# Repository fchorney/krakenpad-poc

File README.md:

# KrakenPad

Open-source dance pad controller hardware and firmware, built for modern ITG-style
rhythm games (Stepmania, ITGmania, DeadSync, etc.).

Commercial dance pad electronics haven't kept pace with what competitive/high-level
play actually wants: low, consistent input latency, high-resolution force sensing,
and hardware/firmware you can actually inspect, modify, and fix yourself. This
project is a ground-up replacement controller — sensor boards, main controller, and
firmware — designed around those priorities instead of around vendor lock-in or
proprietary protocols.

It is not tied to any one game or platform — it just speaks USB HID, so anything
that reads a standard controller/joystick works.

## Priorities

- **Low, consistent input latency.** Presses are detected and reported by dedicated
  interrupt-driven hardware, not discovered via a slow polling cycle — eliminating
  the multi-millisecond blind spots that periodic-scan designs are prone to.
- **High-resolution force sensing.** Each panel reads continuous per-sensor
  pressure (not just a binary switch), sampled at kHz-class rates, enabling more
  accurate and tunable press/release detection than simple threshold switches.
- **Higher, more consistent USB polling and LED refresh rates** than older
  commercial hardware typically offers, for tighter timing and smoother panel
  lighting.
- **Fully open hardware and firmware.** Schematics, PCB layouts, and firmware
  source are all open — no proprietary authentication, no closed protocol, no
  black-box firmware blobs. Anyone can build, modify, or repair their own unit.
- **Standard, open software compatibility.** Presents as a generic USB controller
  so it works out of the box with the open-source rhythm game ecosystem, with no
  vendor-specific driver or SDK required.

## Hardware Scope

The project is initially targeted at retrofitting existing SMX-style dance pad
frames — reusing the frame and panel mechanics while replacing the electronics
(control unit and panel sensor/LED boards) entirely. The design isn't
SMX-compatible at the protocol or hardware level; it simply fits the same
frame as a drop-in electronics replacement, since that's the hardware most
readily available for this kind of upgrade.

## Status

Rev 1 of both boards (the master controller and the two-board panel) was
fabricated in August 2026 and is the hardware in use. A full set of nine panels
and a master run together on the bench: presses reach the PC as a USB joystick,
all nine panels share one RS-485 bus with no errors, and new panel firmware is
flashed to the whole pad over that bus. Written but not yet run on the
hardware: live sensor telemetry and configuration over USB, with the settings
saved on the master. Not written yet: local panel animations. Any board change
from here is a rev 2 change.

Current state and next steps: `docs/STATUS.md`. Per-board results:
`docs/BRINGUP_LOG.md`. Design notes and specs: `CLAUDE.md` and `docs/`.

## AI Disclosure

This project was built with AI assistance (Claude), used mainly for the grunt
work: research and part-comparison legwork, documentation drafts, firmware
prototyping, design-review passes, and scripted KiCad edits/fab outputs. All
design decisions, schematic wiring, PCB layout, and physical testing were done
by a human.

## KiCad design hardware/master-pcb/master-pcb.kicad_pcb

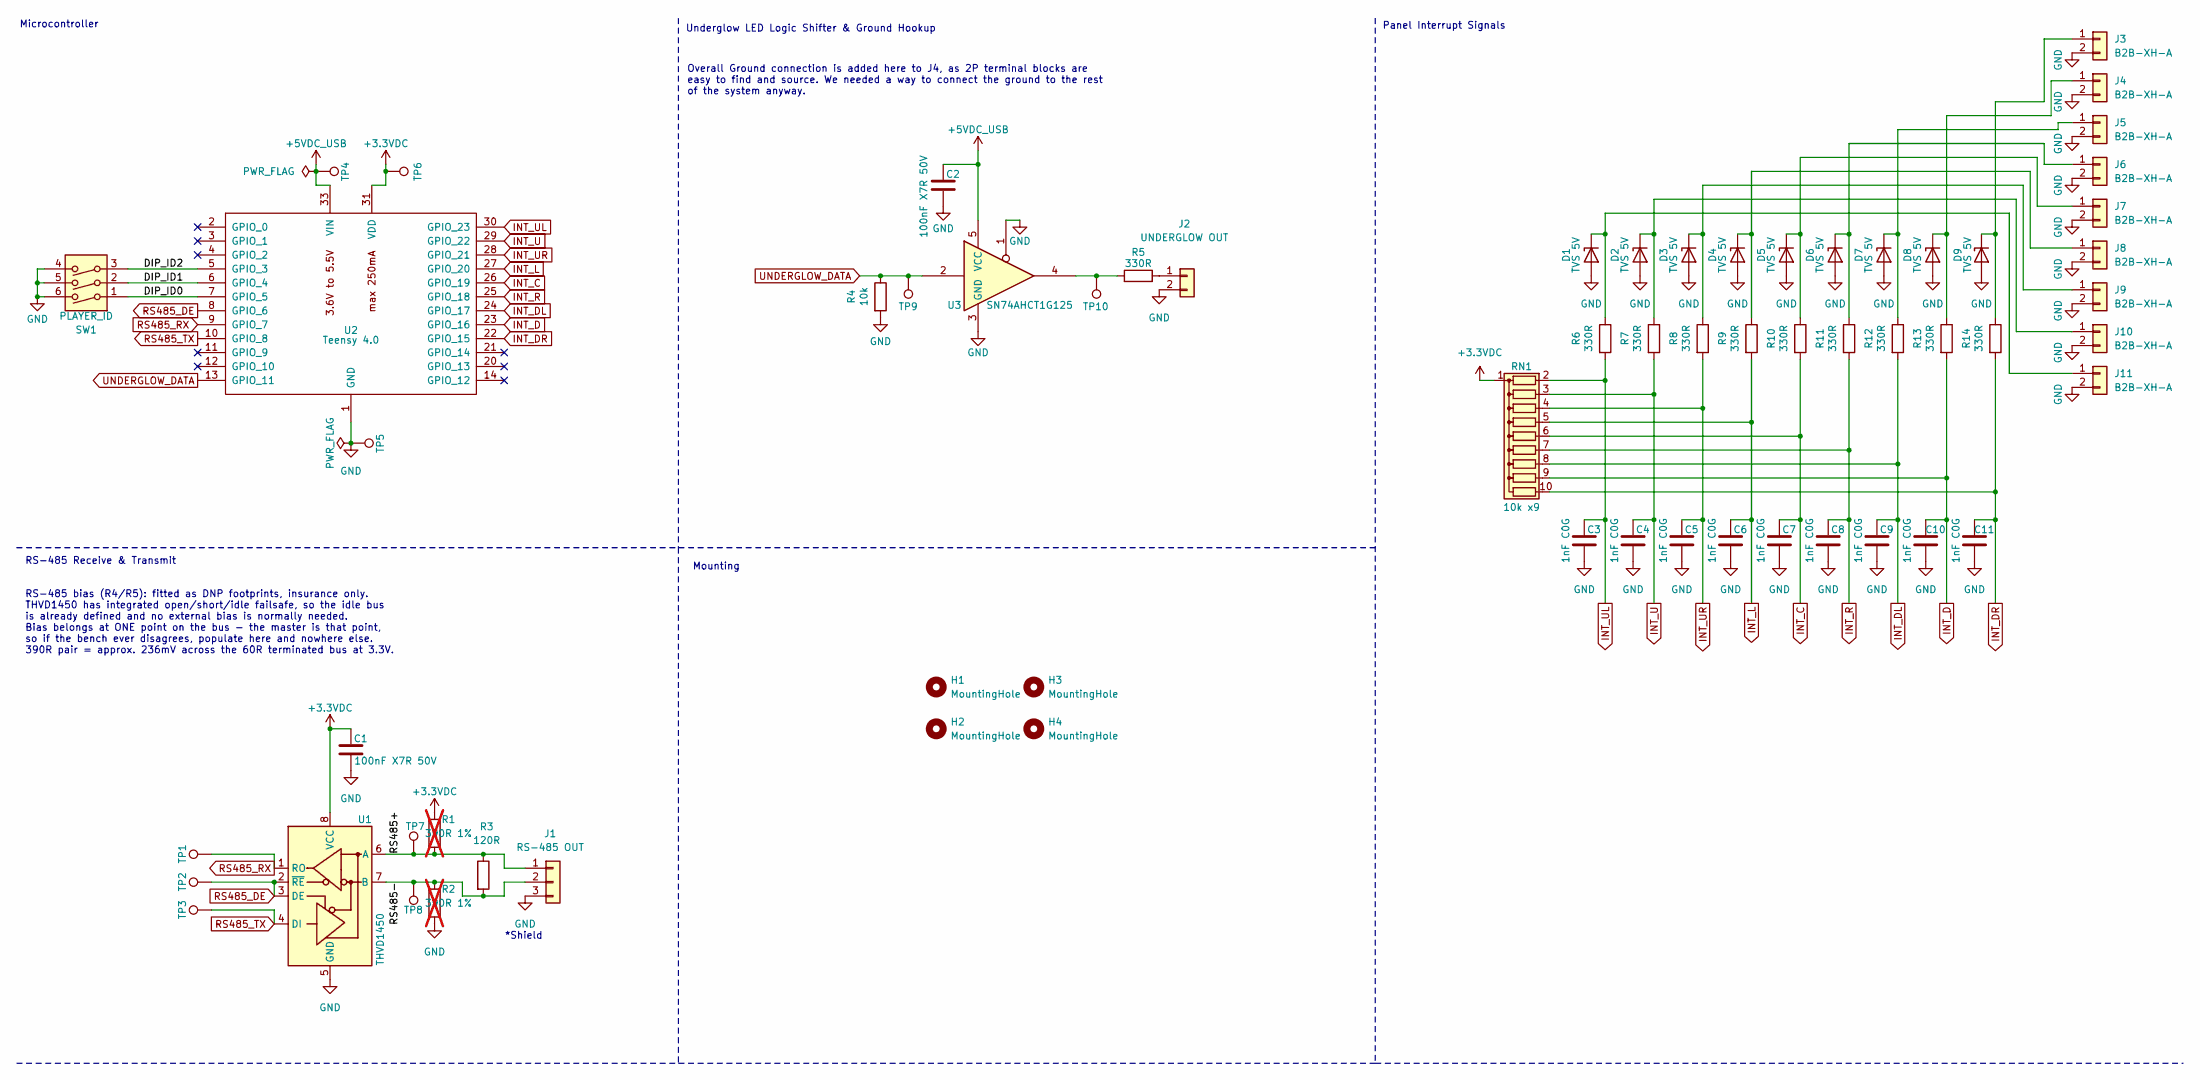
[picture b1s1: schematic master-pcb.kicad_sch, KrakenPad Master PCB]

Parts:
C1, C2: 100nF X7R 50V; C_0805_2012Metric; LCSC C83055
C3, C4, C5, C6, C7, C8, C9, C10, C11: 1nF C0G; C_0805_2012Metric; LCSC C1791
D1, D2, D3, D4, D5, D6, D7, D8, D9: TVS 5V; D_SMA_Handsoldering; MPN SMAJ5.0A; LCSC C113952
H1, H2, H3, H4: MountingHole; MountingHole_3.2mm_M3
J1: RS-485 OUT; Molex_Micro-Fit_3.0_43650-0300_1x03_P3.00mm_Horizontal; MPN 0436500300; LCSC C503478
J2: UNDERGLOW OUT; TerminalBlock_WJ500V-5.08-2P; MPN WJ500V-5.08-2P; LCSC C8465
J3, J4, J5, J6, J7, J8, J9, J10, J11: B2B-XH-A; JST_XH_B2B-XH-A_1x02_P2.50mm_Vertical; LCSC C158012
R1, R2: 390R 1%; R_0805_2012Metric; not fitted
R3: 120R; R_0805_2012Metric; LCSC C844816
R4: 10k; R_0805_2012Metric; LCSC C192906
R5, R6, R7, R8, R9, R10, R11, R12, R13, R14: 330R; R_0805_2012Metric; LCSC C844839
RN1: 10k x9; R_Array_SIP10; MPN 4610X-101-103LF; LCSC C840655
SW1: PLAYER_ID; SW_DIP_SPSTx03_Slide_9.78x9.8mm_W7.62mm_P2.54mm; MPN DS-3P-BU; LCSC C46595747
TP1: RS-485 RX; TestPoint_THTPad_D2.0mm_Drill1.0mm
TP2: RS-485 DE; TestPoint_THTPad_D2.0mm_Drill1.0mm
TP3: RS-485 TX; TestPoint_THTPad_D2.0mm_Drill1.0mm
TP4: +5VDC_USB; TestPoint_THTPad_D2.0mm_Drill1.0mm
TP5: GND; TestPoint_THTPad_D2.0mm_Drill1.0mm
TP6: +3.3VDC; TestPoint_THTPad_D2.0mm_Drill1.0mm
TP7: RS-485 A; TestPoint_THTPad_D2.0mm_Drill1.0mm
TP8: RS-485 B; TestPoint_THTPad_D2.0mm_Drill1.0mm
TP9: Underglow DATA 3.3V; TestPoint_THTPad_D2.0mm_Drill1.0mm
TP10: Underglow DATA 5V; TestPoint_THTPad_D2.0mm_Drill1.0mm
U1: THVD1450; SOIC-8_3.9x4.9mm_P1.27mm; MPN THVD1450DR; LCSC C2671361
U2: Teensy 4.0; Teensy40_Socketed; MPN 15583; DigiKey 1568-15583-ND
U3: SN74AHCT1G125; SOT-23-5; MPN SN74AHCT1G125DBVR; LCSC C7484

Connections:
+3.3VDC: C1.1, R1.1, RN1.1 (common), TP6.1 (1_1), U1.8 (VCC), U2.31 (VDD)
+5VDC_USB: C2.1, TP4.1 (1_1), U2.33 (VIN), U3.5 (VCC)
/DIP_ID0: SW1.1, U2.7 (GPIO_5)
/DIP_ID1: SW1.2, U2.6 (GPIO_4)
/DIP_ID2: SW1.3, U2.5 (GPIO_3)
/RS485+: J1.1, R1.2, R3.1, TP7.1 (1_1), U1.6 (A)
/RS485-: J1.2, R2.1, R3.2, TP8.1 (1_1), U1.7 (B)
GND: C1.2, C2.2, C3.2, C4.2, C5.2, C6.2, C7.2, C8.2, C9.2, C10.2, C11.2, D1.2 (A), D2.2 (A), D3.2 (A), D4.2 (A), D5.2 (A), D6.2 (A), D7.2 (A), D8.2 (A), D9.2 (A), J1.3, J2.2, J3.2, J4.2, J5.2, J6.2, J7.2, J8.2, J9.2, J10.2, J11.2, R2.2, R4.2, SW1.4, SW1.5, SW1.6, TP5.1 (1_1), U1.5 (GND), U2.1 (GND), U2.32 (GND), U3.1, U3.3 (GND)
INT_C: C7.1, R10.2, RN1.6 (R5), U2.26 (GPIO_19)
INT_D: C10.1, R13.2, RN1.9 (R8), U2.23 (GPIO_16)
INT_DL: C9.1, R12.2, RN1.8 (R7), U2.24 (GPIO_17)
INT_DR: C11.1, R14.2, RN1.10 (R9), U2.22 (GPIO_15)
INT_L: C6.1, R9.2, RN1.5 (R4), U2.27 (GPIO_20)
INT_R: C8.1, R11.2, RN1.7 (R6), U2.25 (GPIO_18)
INT_U: C4.1, R7.2, RN1.3 (R2), U2.29 (GPIO_22)
INT_UL: C3.1, R6.2, RN1.2 (R1), U2.30 (GPIO_23)
INT_UR: C5.1, R8.2, RN1.4 (R3), U2.28 (GPIO_21)
unnamed: D1.1 (K), J11.1, R6.1
unnamed: D2.1 (K), J10.1, R7.1
unnamed: D3.1 (K), J9.1, R8.1
unnamed: D4.1 (K), J8.1, R9.1
unnamed: D5.1 (K), J7.1, R10.1
unnamed: D6.1 (K), J6.1, R11.1
unnamed: D7.1 (K), J5.1, R12.1
unnamed: D8.1 (K), J4.1, R13.1
unnamed: D9.1 (K), J3.1, R14.1
unnamed: J2.1, R5.2
unnamed: R5.1, TP10.1 (1_1), U3.4
RS485_DE: TP2.1 (1_1), U1.2 (~RE), U1.3 (DE), U2.8 (GPIO_6)
RS485_RX: TP1.1 (1_1), U1.1 (RO), U2.9 (GPIO_7)
RS485_TX: TP3.1 (1_1), U1.4 (DI), U2.10 (GPIO_8)
UNDERGLOW_DATA: R4.1, TP9.1 (1_1), U2.13 (GPIO_11), U3.2

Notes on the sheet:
Panel Interrupt Signals
RS-485 bias (R4/R5): fitted as DNP footprints, insurance only. THVD1450 has integrated open/short/idle failsafe, so the idle bus is already defined and no external bias is normally needed. Bias belongs at ONE point on the bus - the master is that point, so if the bench ever disagrees, populate here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
Overall Ground connection is added here to J4, as 2P terminal blocks are easy to find and source. We needed a way to connect the ground to the rest of the system anyway.
Mounting
*Shield
Underglow LED Logic Shifter & Ground Hookup
Microcontroller
RS-485 Receive & Transmit

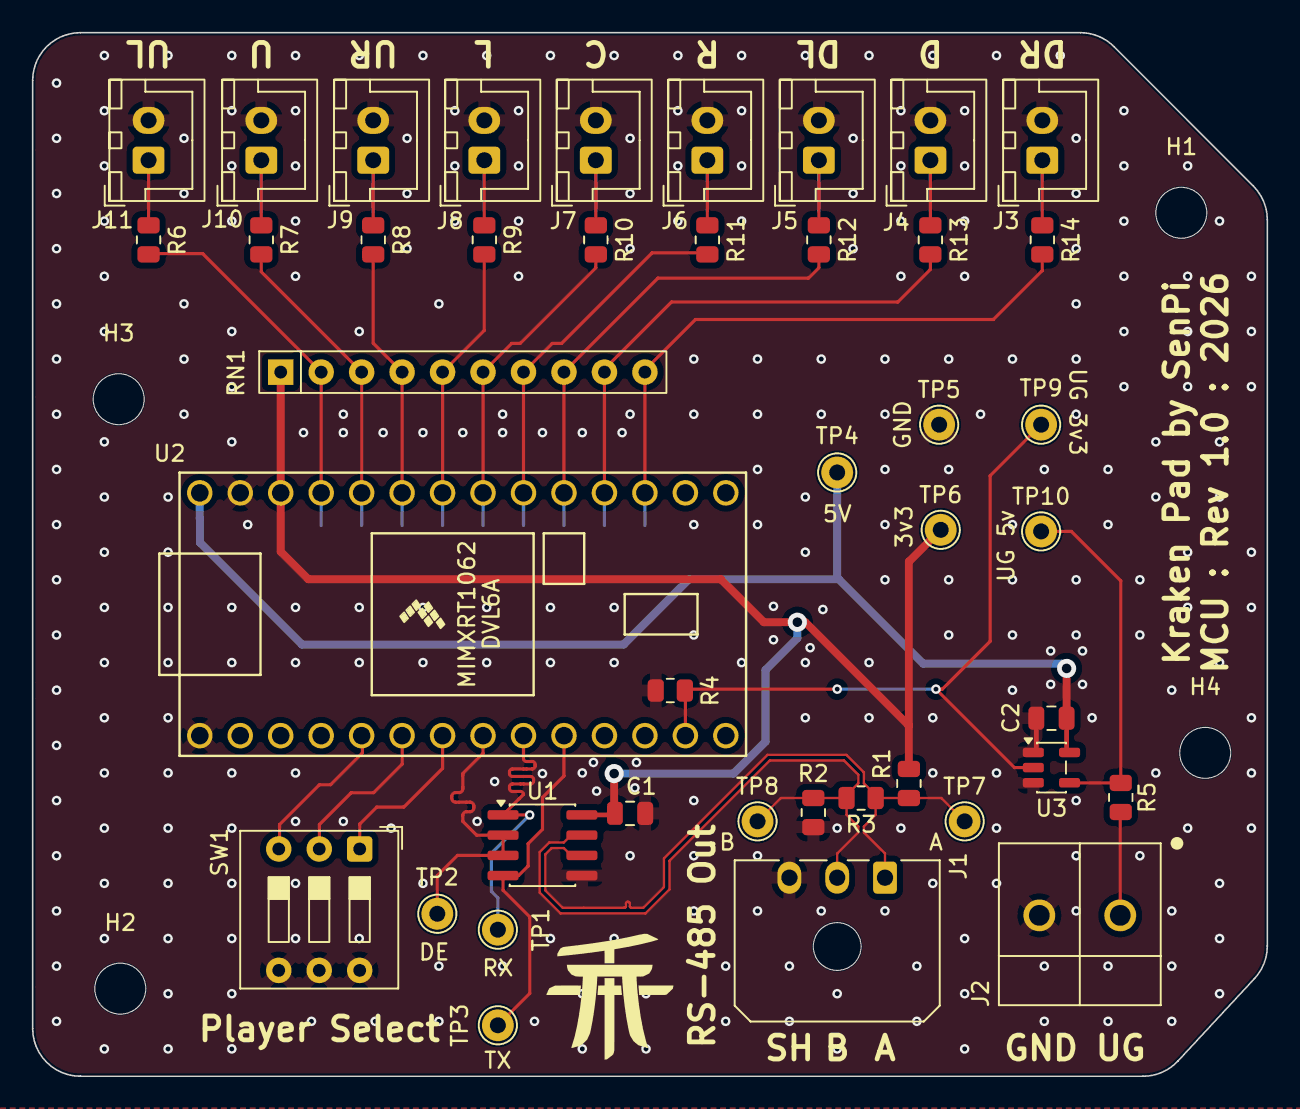
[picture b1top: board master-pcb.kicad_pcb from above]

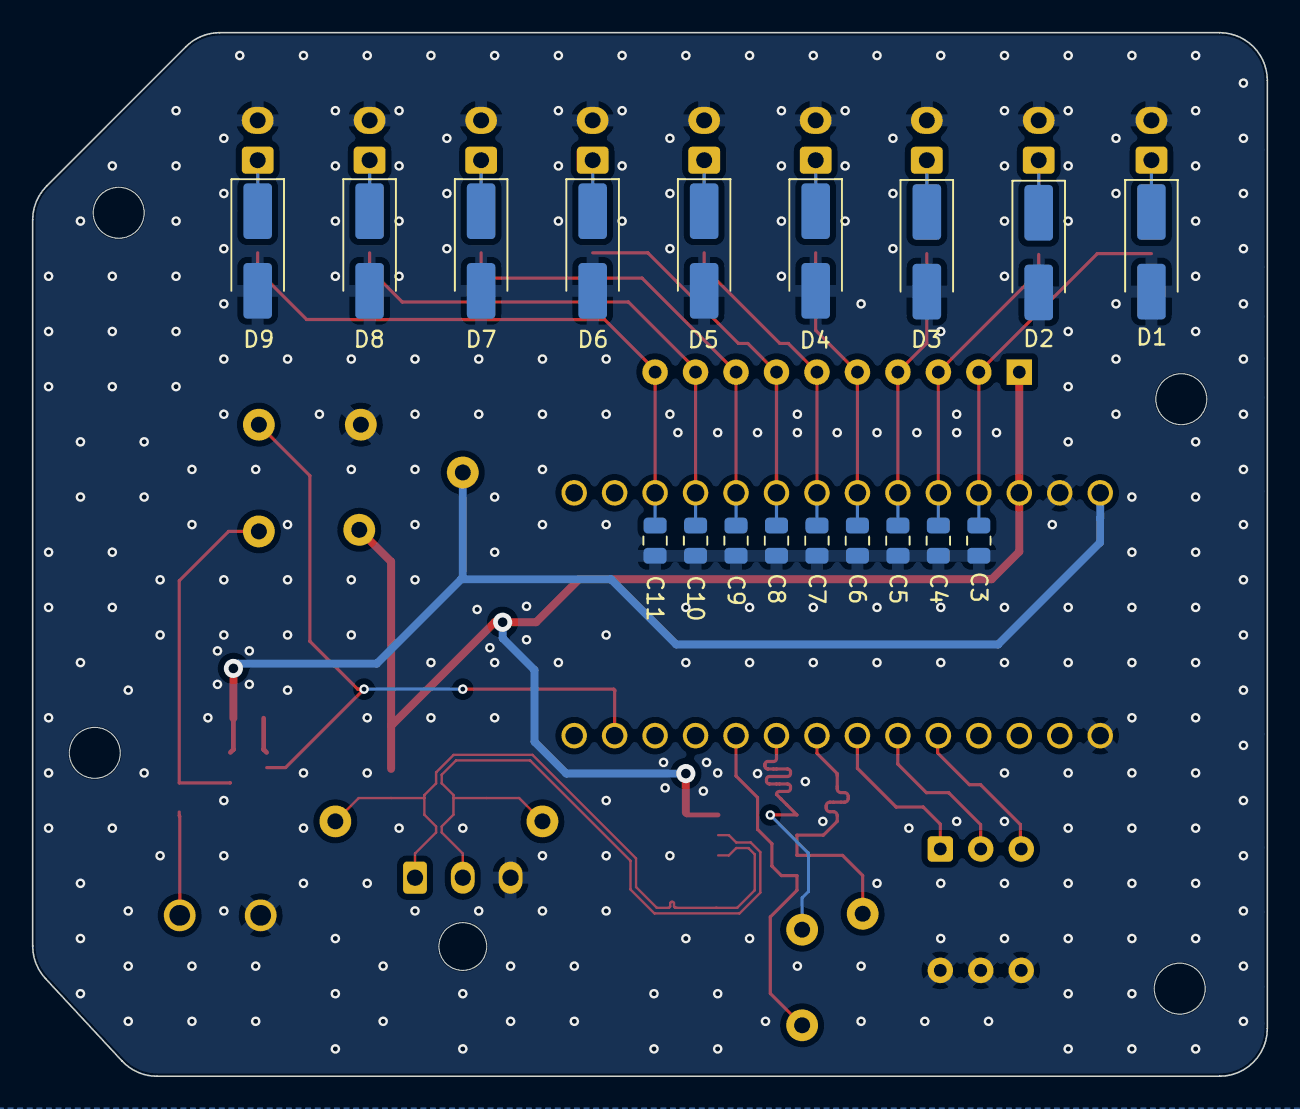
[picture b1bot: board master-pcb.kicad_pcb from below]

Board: 4 copper layers, 77.5 x 65.5 mm, 64 parts (18 on the bottom side), 32 nets.

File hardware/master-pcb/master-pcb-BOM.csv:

Qty,Refs,Value,LCSC,MPN,Source,DNP,Description
2,C1 C2,100nF X7R 50V,C83055,,LCSC,,2 per-instance descriptions
9,C3 C4 C5 C6 C7 C8 C9 C10 C11,1nF C0G,C1791,,LCSC,,9 per-instance descriptions
9,D1 D2 D3 D4 D5 D6 D7 D8 D9,TVS 5V,C113952,SMAJ5.0A,LCSC,,9 per-instance descriptions
1,J1,RS-485 OUT,C503478,0436500300,LCSC,,"Micro-Fit 3.0 THT right-angle 43650-0300; pin 3 = cable shield, tied directly to GND here; pinout must match panel J204/J207 (A=1,B=2)"
1,J2,UNDERGLOW OUT,C8465,WJ500V-5.08-2P,LCSC,,"KANGNEX WJ500V-5.08-2P (LCSC C8465), 2P 5.08mm top-entry screw terminal: GND + LED-DATA-OUT (5V logic). UI-gated; no sense pin"
9,J3 J4 J5 J6 J7 J8 J9 J10 J11,B2B-XH-A,C158012,,LCSC,,JST XH B2B-XH-A
2,R1 R2,390R 1%,,,not stocked,DNP,2 per-instance descriptions
1,R3,120R,C844816,,LCSC,,"RS-485 termination at master end, always fitted"
1,R4,10k,C192906,,LCSC,,Underglow Data Out Pulldown: To avoid sending stray high logic to Underglow LEDs before initialized.
10,R5 R6 R7 R8 R9 R10 R11 R12 R13 R14,330R,C844839,,LCSC,,10 per-instance descriptions
1,RN1,10k x9,C840655,4610X-101-103LF,LCSC,,"INT pull-ups to 3.3V, deliberately 10k not stiff (INT-into-dead-panel case); common pin to +3V3"
1,SW1,PLAYER_ID,C46595747,DS-3P-BU,LCSC,,"3-bit player/pad ID to GND, Teensy internal pull-ups; 0-3=P1-P4, 4-7 reserved"
1,U1,THVD1450,C2671361,THVD1450DR,LCSC,,"RS-485 transceiver, 3.3V; DE+/RE tied to GPIO2 net; same MPN as panel U2"
1,U2,Teensy 4.0,,15583,DigiKey,,"Teensy 4.0 development board (600MHz Cortex-M7, socketed). Symbol vendored from XenGi/teensy_library (MIT), pin numbering per PJRC pinout cards rev2; pins renamed/relaid for this project. Pins 35-54 (bottom-side SMT pads) and 15-19 (the 5-pad short-end row: VBAT, VDD, GND, PROGRAM, ON_OFF) removed to match the Teensy40_Socketed footprint and keep schematic-parity clean. 15-19 dropped 2026-07-22 to free routing area: 16/17 were stacked duplicates of the VDD/GND on pins 31/1/32, and VBAT/PROGRAM/ON_OFF are unused on this design."
1,U3,SN74AHCT1G125,C7484,SN74AHCT1G125DBVR,LCSC,,Single Bus Buffer Gate With 3-State Output

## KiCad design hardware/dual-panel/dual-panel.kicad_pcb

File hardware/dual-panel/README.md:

# Dual-board panel — the panel design

**This is the panel in use (rev 1, nine assembled).** The single-board alternative
(`hardware/panel-pcb`) was retired on 2026-08-04; it lives in git history only,
last present at `1b41d1c`.

**For as-built facts — interface pin map, RP2040 GPIO map, part inventory,
mechanical stack, verification status — read [`docs/DUAL_PANEL.md`](../../docs/DUAL_PANEL.md).**
This file covers only *why the project is shaped the way it is*; anything
enumerable is derived from the KiCad files and lives in that doc, so it cannot
drift.

> Earlier revisions of this file described a 34-pin two-row interface (J12/J13),
> USB-C on the carrier, and two mounting screws. **None of that was built.** The
> interface is four 1×8 rows (32 pins), USB-C is on the brain, and there are three
> screws. Trust `docs/DUAL_PANEL.md`.

## The idea

Split the 127×127 mm panel into a **display/IO carrier** — 25 WS2815s, every
external connector, the switches — and a **brain** — RP2040, flash, transceiver,
regulators, level shifter, USB — that plugs into the carrier's underside and sits
in the frame cavity. The LEDs own the top surface; anything mounted above them
shadows the play surface.

Motivations, in the order they mattered:

1. **Layout separation.** On one board the LED field and the brain compete for the
   same planes. Split, each board's routing is a different problem.
2. **ESD and protection.** Clamp at the ports on the carrier; the brain sits behind
   the connector.
3. **Fix the brain without re-fabbing the panels.** Not about upgrades — about a
   routing or hardware bug found at bring-up. Re-spinning a small brain board is far
   cheaper in money and materials than re-spinning 20 carriers.

The measured comparison that settled single-vs-dual is archived at
[`docs/archive/DESIGN_COMPARISON.md`](../../docs/archive/DESIGN_COMPARISON.md). Short
version: cost was near-neutral at **$2.13/panel**, and the split measured *better*
on FSR isolation — 1.1× channel-length spread vs 11×, and 3.18 mm worst same-layer
clearance to LED data / 12V vs 1.06 mm.

## Why one KiCad project rather than two

KiCad has no multi-board feature, but a project is already *one hierarchy → one
netlist → one `.kicad_pcb`*, and two `Edge.Cuts` outlines in a single board file is
the supported way to panelise. Two things fall out:

- **ERC checks the board-to-board interface for you.** With two separate projects,
  every interface change means editing two schematics and hand-checking that they
  agree — and the interface spec is precisely the mistake that would force *both*
  boards to be re-spun.
- **One JLC engineering fee and one PCBA setup instead of two.**

The cost is a known wart: the ratsnest draws airwires across the mating gap and DRC
reports 19 `unconnected_items`. There is no way to tell KiCad "these mate
mechanically." Giving each side distinct net names would kill the airwires but throw
away the cross-checking that motivated this structure, so the 19 are accepted and
enumerated instead.

## Why both boards are 4-layer on one panel

Tempting idea: carrier at 2 layers, brain at 4, since the carrier looks like it
might route single-sided. It costs more, not less, and it is not close.

A 2-layer carrier saves only the bare-fab delta on one board — the qty-5 quote put
the *entire* board cost for the 127×127 4-layer panel at **$14.91**, so even if
2-layer PCBs were free the saving caps around **$55** at qty 20; realistically
**$25–35**. A second run costs fixed per-order overhead: $25 eng fee + $51.12 PCBA
setup + $16.42 stencil + $4.93 storage ≈ **$97**, plus a second ~$40 shipment ⇒
**~$137**.

| | one 4L panel (both boards) | 2L carrier + 4L brain |
|---|---|---|
| bare fab | ~$55–60 | ~$25–30 + ~$15 |
| order overhead | $97 × 1 | $97 × 2 |
| shipping | ~$40 | ~$80 |
| **net** | — | **~$110–140 worse** |

There is no quantity where this flips: the saving scales with board count, the
penalty doesn't. Both boards need PCBA regardless — WS2815 is MSL 5a with a 24 h
floor life, so hand-assembling the carrier was never on the table.

What you get for the $25–35 you'd have "saved" is two extra copper layers on the
noisiest board in the system: an uninterrupted GND plane plus a power plane, under a
25-LED field with four high-impedance FSR lines crossing it. That is motivation #1
delivered better than the 2-layer version would have.

**6-layer was the weakest option considered** — JLCPCB lists 4-layer 100×100 mm from
~$7 vs 6-layer from ~$35, and it delivers neither the best routing environment nor
fault isolation. Only a 6-layer *brain* would genuinely force two fab runs; the brain
is already 4-layer-proven, since all of its content routed on 4 layers back when it
was still sharing them with the LED field and 12V distribution.

*Prices are point-in-time — verify live (`docs/FAB_ORDER.md` → "Money").*

## Directory map

| path | what |
|---|---|
| `dual-panel.kicad_sch` | root sheet — two sheet symbols, nothing else |
| `carrier.kicad_sch` / `brain.kicad_sch` | the two roles |
| `dual-panel.kicad_pcb` | **both** outlines, carrier left of x=182.55 mm, brain right |
| `dual-panel.pretty` / `.kicad_sym` / `3dmodels/` | project-local libraries |
| `panel/` | panelisation + JLC fab package — `gen_panel.py`, `gen_fab.py` (quotes are in `docs/rev1-order/`) |
| `fit-test/` | 1:1 printable cavity fit template — re-run after any outline change |

Both sheets were seeded as full copies of `panel-pcb` rev 1.0 and stripped to role,
which is why some schematic sheet descriptions still say so. That is history, not a
live dependency: **`dual-panel` references no `panel-pcb` library**, and its
`fp-lib-table`/`sym-lib-table` point only at its own project-local libs.

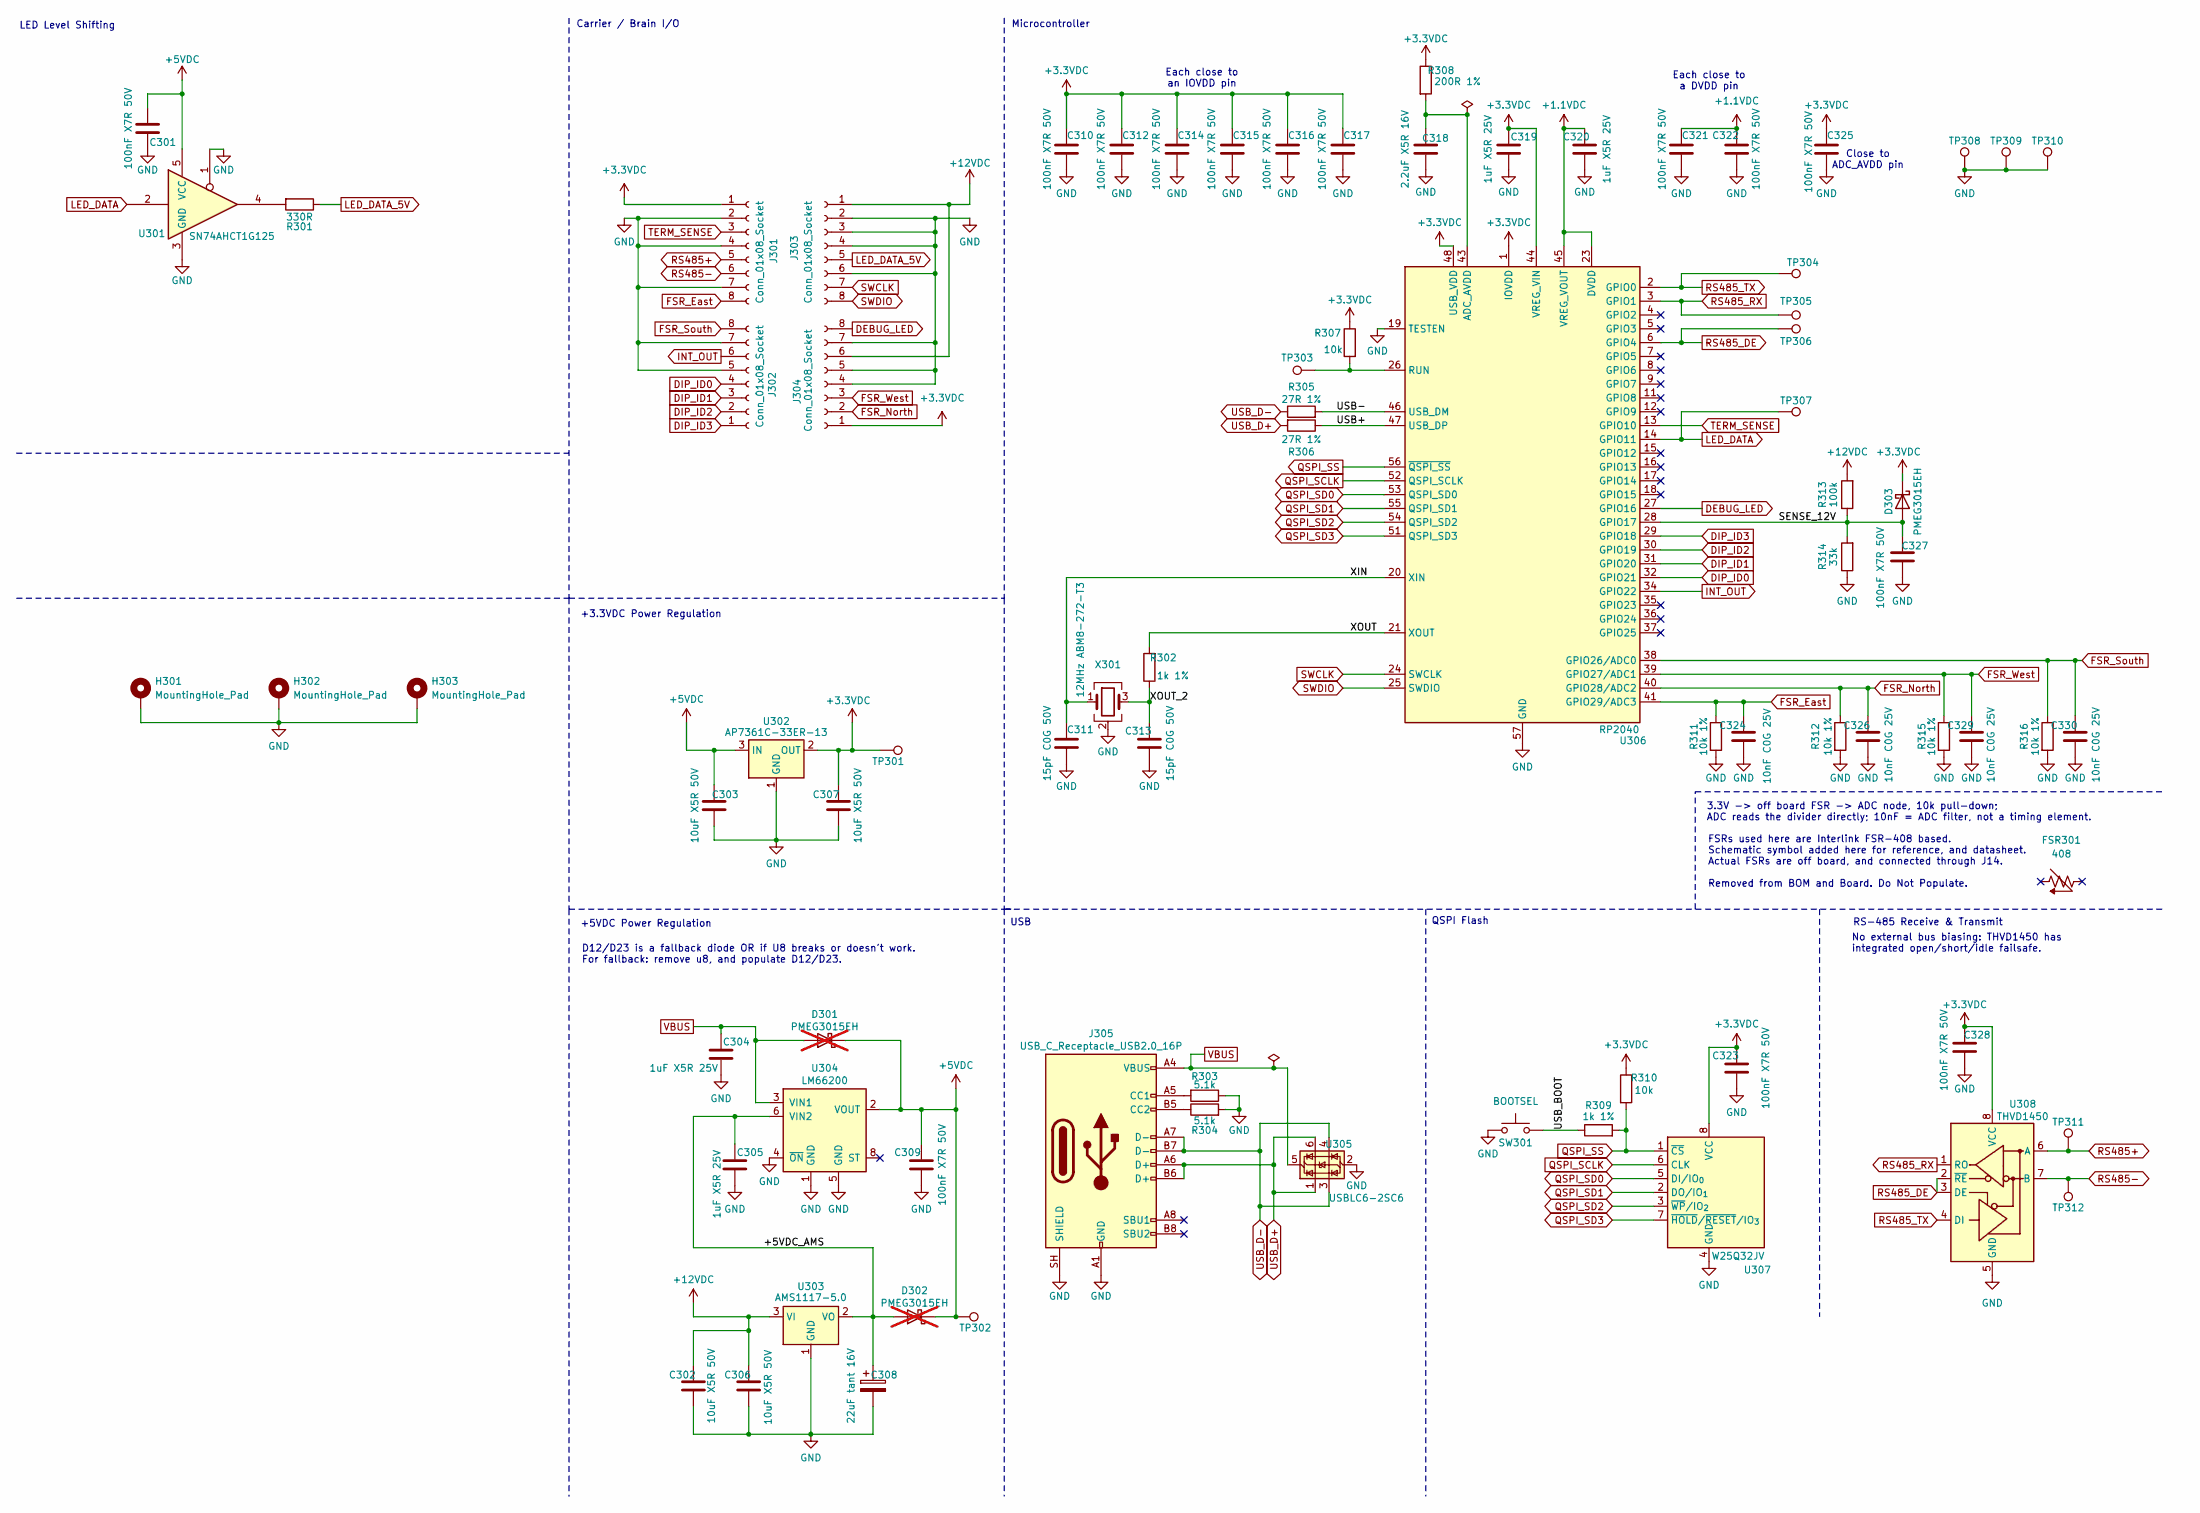
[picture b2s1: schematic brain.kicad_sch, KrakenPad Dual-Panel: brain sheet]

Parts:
C301, C323, C327, C328: 100nF X7R 50V; C_0603_1608Metric; LCSC C14663
C302, C303, C306, C307: 10uF X5R 50V; C_0805_2012Metric; LCSC C440198
C304, C305, C319, C320: 1uF X5R 25V; C_0402_1005Metric_SilkTrim; LCSC C52923
C308: 22uF tant 16V; CP_EIA-3528-21_Kemet-B; MPN TAJB226K016RNJ; LCSC C8020
C309, C310, C312, C314, C315, C316, C317, C321, C322, C325: 100nF X7R 50V; C_0402_1005Metric_SilkTrim; LCSC C307331
C311, C313: 15pF C0G 50V; C_0603_1608Metric; LCSC C1644
C318: 2.2uF X5R 16V; C_0402_1005Metric_SilkTrim; LCSC C170151
C324, C326, C329, C330: 10nF C0G 25V; C_0603_1608Metric; LCSC C723749
D301, D302: PMEG3015EH; D_SOD-123F; MPN PMEG3015EH,115; LCSC C552867; not fitted
D303: PMEG3015EH; D_SOD-123F; MPN PMEG3015EH,115; LCSC C552867
FSR301: 408
H301, H302, H303: MountingHole_Pad; MountingHole_3.2mm_M3_Pad
J301, J302, J303, J304: Conn_01x08_Socket; PinSocket_1x08_P2.54mm_Vertical
J305: USB_C_Receptacle_USB2.0_16P; USB_C_Receptacle_GCT_USB4085_EdgeTrim; MPN USB4085-GF-A; LCSC C7095263
R301: 330R; R_0603_1608Metric; LCSC C23138
R302, R309: 1k 1%; R_0603_1608Metric; LCSC C2907002
R303, R304: 5.1k; R_0603_1608Metric; LCSC C23186
R305, R306: 27R 1%; R_0603_1608Metric; LCSC C25190
R307, R310: 10k; R_0603_1608Metric; LCSC C2906982
R308: 200R 1%; R_0603_1608Metric; LCSC C8218
R311, R312, R315, R316: 10k 1%; R_0603_1608Metric; LCSC C98220
R313: 100k; R_0603_1608Metric; LCSC C25803
R314: 33k; R_0603_1608Metric; LCSC C4216
SW301: BOOTSEL; SW_SPST_B3U-1000P; MPN B3U-1000P; LCSC C231329
TP301: +3.3VDC; TestPoint_THTPad_D2.0mm_Drill1.0mm
TP302: +5VDC; TestPoint_THTPad_D2.0mm_Drill1.0mm
TP303: RUN; TestPoint_THTPad_D2.0mm_Drill1.0mm
TP304: UART TX; TestPoint_THTPad_D2.0mm_Drill1.0mm
TP305: UART RX; TestPoint_THTPad_D2.0mm_Drill1.0mm
TP306: RS-485 DE; TestPoint_THTPad_D2.0mm_Drill1.0mm
TP307: LED Data 3.3V; TestPoint_THTPad_D2.0mm_Drill1.0mm
TP308, TP309, TP310: GND; TestPoint_THTPad_D2.0mm_Drill1.0mm
TP311: RS485+; TestPoint_THTPad_D2.0mm_Drill1.0mm
TP312: RS485-; TestPoint_THTPad_D2.0mm_Drill1.0mm
U301: SN74AHCT1G125; SOT-23-5; MPN SN74AHCT1G125DBVR; LCSC C7484
U302: AP7361C-33ER-13; SOT-223-3_TabPin2; MPN AP7361C-33ER-13; LCSC C3743528
U303: AMS1117-5.0; SOT-223-3_TabPin2; MPN AMS1117-5.0; LCSC C6187
U304: LM66200; SOT-583-8; MPN LM66200DRLR; LCSC C3235556
U305: USBLC6-2SC6; SOT-23-6; MPN USBLC6-2SC6; LCSC C2827654
U306: RP2040; QFN-56-1EP_7x7mm_P0.4mm_EP3.2x3.2mm_RPiPad; MPN RP2040; LCSC C2040
U307: W25Q32JV; SOIC-8_5.3x5.3mm_P1.27mm; MPN W25Q32JVSSIQ; LCSC C179173
U308: THVD1450; SOIC-8_3.9x4.9mm_P1.27mm; MPN THVD1450DR; LCSC C2671361
X301: 12MHz ABM8-272-T3; Crystal_SMD_3225-4Pin_3.2x2.5mm; MPN ABM8-272-T3; LCSC C20625731

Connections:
+1.1VDC: C320.1, C321.1, C322.1, U306.23 (DVDD), U306.45 (VREG_VOUT), U306.50 (DVDD)
+3.3VDC: C307.1, C310.1, C312.1, C314.1, C315.1, C316.1, C317.1, C319.2, C323.1, C325.1, C328.1, D303.1 (K), J301.1, J304.1, R307.1, R308.1, R310.1, TP301.1 (1_1), U302.2 (OUT), U306.1 (IOVDD), U306.10 (IOVDD), U306.22 (IOVDD), U306.33 (IOVDD), U306.42 (IOVDD), U306.44 (VREG_VIN), U306.48 (USB_VDD), U306.49 (IOVDD), U307.8 (VCC), U308.8 (VCC); also elsewhere on the board
+5VDC: C301.1, C303.1, C309.1, D301.1 (K), D302.1 (K), TP302.1 (1_1), U301.5 (VCC), U302.3 (IN), U304.2 (VOUT), U304.7 (VOUT)
+12VDC: C302.1, C306.1, J303.1, J304.6, R313.2, U303.3 (VI); also elsewhere on the board
/brain/+5VDC_AMS: C305.2, C308.1, D302.2 (A), U303.2 (VO), U304.6 (VIN2)
/brain/SENSE_12V: C327.2, D303.2 (A), R313.1, R314.2, U306.28 (GPIO17)
/brain/USB+: R306.1, U306.47 (USB_DP)
/brain/USB-: R305.2, U306.46 (USB_DM)
/brain/USB_BOOT: R309.1, SW301.1
/brain/XIN: C311.1, U306.20 (XIN), X301.1
/brain/XOUT: R302.2, U306.21 (XOUT)
/brain/XOUT_2: C313.1, R302.1, X301.3
DEBUG_LED: J304.8, U306.27 (GPIO16); also elsewhere on the board
DIP_ID0: J302.4, U306.32 (GPIO21); also elsewhere on the board
DIP_ID1: J302.3, U306.31 (GPIO20); also elsewhere on the board
DIP_ID2: J302.2, U306.30 (GPIO19); also elsewhere on the board
DIP_ID3: J302.1, U306.29 (GPIO18); also elsewhere on the board
FSR_East: C324.1, J301.8, R311.1, U306.41 (GPIO29/ADC3); also elsewhere on the board
FSR_North: C326.1, J304.2, R312.1, U306.40 (GPIO28/ADC2); also elsewhere on the board
FSR_South: C330.1, J302.8, R316.1, U306.38 (GPIO26/ADC0); also elsewhere on the board
FSR_West: C329.1, J304.3, R315.1, U306.39 (GPIO27/ADC1); also elsewhere on the board
GND: C301.2, C302.2, C303.2, C304.1, C305.1, C306.2, C307.2, C308.2, C309.2, C310.2, C311.2, C312.2, C313.2, C314.2, C315.2, C316.2, C317.2, C318.1, C319.1, C320.2, C321.2, C322.2, C323.2, C324.2, C325.2, C326.2, C327.1, C328.2, C329.2, C330.2, H301.1 (1_1), H302.1 (1_1), H303.1 (1_1), J301.2, J301.4, J301.7, J302.5, J302.7, J303.2, J303.3, J303.4, J303.6, J304.4, J304.5, J304.7, J305.A1 (GND), J305.A12 (GND), J305.B1 (GND), J305.B12 (GND), J305.SH (SHIELD), R303.1, R304.2, R311.2, R312.2, R314.1, R315.2, R316.2, SW301.2, TP308.1 (1_1), TP309.1 (1_1), TP310.1 (1_1), U301.1, U301.3 (GND), U302.1 (GND), U303.1 (GND), U304.1 (GND), U304.4 (~ON), U304.5 (GND), U305.2 (GND), U306.19 (TESTEN), U306.57 (GND), U307.4 (GND), U308.5 (GND), X301.2 (G), X301.4 (G); also elsewhere on the board
INT_OUT: J302.6, U306.34 (GPIO22); also elsewhere on the board
LED_DATA: TP307.1 (1_1), U301.2, U306.14 (GPIO11)
LED_DATA_5V: J303.5, R301.1; also elsewhere on the board
unnamed: J305.A5 (CC1), R303.2
unnamed: J305.B5 (CC2), R304.1
unnamed: R301.2, U301.4
unnamed: C318.2, R308.2, U306.43 (ADC_AVDD)
unnamed: R307.2, TP303.1 (1_1), U306.26 (RUN)
QSPI_SCLK: U306.52 (QSPI_SCLK), U307.6 (CLK)
QSPI_SD0: U306.53 (QSPI_SD0), U307.5 (DI/IO_{0})
QSPI_SD1: U306.55 (QSPI_SD1), U307.2 (DO/IO_{1})
QSPI_SD2: U306.54 (QSPI_SD2), U307.3 (~WP/IO_{2})
QSPI_SD3: U306.51 (QSPI_SD3), U307.7 (~HOLD/~RESET/IO_{3})
QSPI_SS: R309.2, R310.2, U306.56 (~QSPI_SS), U307.1 (~CS)
RS485+: J301.5, TP311.1 (1_1), U308.6 (A); also elsewhere on the board
RS485-: J301.6, TP312.1 (1_1), U308.7 (B); also elsewhere on the board
RS485_DE: TP306.1 (1_1), U306.6 (GPIO4), U308.2 (~RE), U308.3 (DE)
RS485_RX: TP305.1 (1_1), U306.3 (GPIO1), U308.1 (RO)
RS485_TX: TP304.1 (1_1), U306.2 (GPIO0), U308.4 (DI)
SWCLK: J303.7, U306.24 (SWCLK); also elsewhere on the board
SWDIO: J303.8, U306.25 (SWDIO); also elsewhere on the board
TERM_SENSE: J301.3, U306.13 (GPIO10); also elsewhere on the board
USB_D+: J305.A6 (D+), J305.B6 (D+), R306.2, U305.1 (I/O1), U305.6 (I/O1)
USB_D-: J305.A7 (D-), J305.B7 (D-), R305.1, U305.3 (I/O2), U305.4 (I/O2)
VBUS: C304.2, D301.2 (A), J305.A4 (VBUS), J305.A9 (VBUS), J305.B4 (VBUS), J305.B9 (VBUS), U304.3 (VIN1), U305.5 (VBUS)

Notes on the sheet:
+5VDC Power Regulation
QSPI Flash
Microcontroller
+3.3VDC Power Regulation
No external bus biasing: THVD1450 has integrated open/short/idle failsafe.
Carrier / Brain I/O
D12/D23 is a fallback diode OR if U8 breaks or doesn't work. For fallback: remove u8, and populate D12/D23.
RS-485 Receive & Transmit
USB
FSRs used here are Interlink FSR-408 based. Schematic symbol added here for reference, and datasheet. Actual FSRs are off board, and connected through J14. Removed from BOM and Board. Do Not Populate.
3.3V -> off board FSR -> ADC node, 10k pull-down; ADC reads the divider directly; 10nF = ADC filter, not a timing element.
LED Level Shifting
Each close to an IOVDD pin
Each close to a DVDD pin
Close to ADC_AVDD pin
